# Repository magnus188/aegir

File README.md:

Ægir is a work-in-progress trimix gas analyzer for technical diving. It is not
qualified as a breathing-gas safety instrument; use it at your own risk.

Made in Norway 🇳🇴.

## The name

In Norse mythology, Ægir (/ˈæːɣir/) is the giant who rules the sea. He is
known for hosting the gods in his halls adorned with gold and, together with
Rán, is the father of nine daughters who personify the waves.

The runes ᛅᛁᚾ are a Viking Age-style representation of einn, Old Norse for
“one”, marking the first version of the project: Ægir 1.

## Features

- Oxygen (O₂) and helium (He) sensor inputs, plus CO monitoring
- 4.3-inch touch screen for gas analysis, calibration and settings
- Mix calculations, dive planning and analysis history
- Desktop simulator with demo readings

**[Try the interactive browser demo](https://magnus188.github.io/aegir/).**

## Device design

*CAD-based render of the current prototype.*

## Screenshots

These screens show the simulator with demo data.

| Main menu | Live analysis | Analysis details |
| :---: | :---: | :---: |
|  |  |  |

| History | Cylinders | Settings |
| :---: | :---: | :---: |
|  |  |  |

| Dive Planner | Device Settings |
| :---: | :---: |
|  |  |

| Simulated high CO alert | Safety Settings |
| :---: | :---: |
|  |  |

## Run it

For the desktop simulator, install a C++ compiler, CMake, `pkg-config` and SDL2,
then run from the repository root:

```sh
make sim-deps
make sim ZOOM=0.75
```

Run the host tests with `make test`.

To build and flash the firmware on the Guition JC4880P443C_I_W ESP32-P4 board,
install Python 3.13 and run:

```sh
make setup-idf
make devices
make board-info PORT=/dev/cu.usbserial-110
make push PORT=/dev/cu.usbserial-110
```

Replace the example `PORT` with the port reported by `make devices`. See the
[firmware guide](software/firmware/README.md) for other build options.

## Contributing and future ideas

Design reviews, measurements, documentation and software fixes are welcome.
Start with the [contribution guide](CONTRIBUTING.md) and
[open issues](https://github.com/magnus188/aegir/issues). The
[v2 investigation backlog](https://github.com/magnus188/aegir/milestone/1)
collects community suggestions without promising a release date.

Maintainers can use the [repository guide](.github/MAINTAINING.md). For
exploitable vulnerabilities, use the [private reporting route](SECURITY.md).

## Acknowledgements

A big thank you to [@tobiasruber](https://github.com/tobiasruber) for reviewing and
improving the PCB design. His help is a big reason this project is still alive
and moving forward.

## License

Software: [GPLv3](LICENSES/GPL-3.0-only.txt). PCB and CAD files:
[CERN-OHL-S-2.0](LICENSES/CERN-OHL-S-2.0.txt). The Ægir name and logo have a
separate [brand policy](logo/LICENSE.md). See the [license map](LICENSE.md)
for details and third-party files.

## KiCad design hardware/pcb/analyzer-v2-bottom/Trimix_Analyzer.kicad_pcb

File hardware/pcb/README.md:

# PCB designs

Open the active KiCad projects from their source folders:

| Board | Project | Purpose |
| --- | --- | --- |
| Main analyzer | [Trimix_Analyzer.kicad_pro](analyzer/Trimix_Analyzer.kicad_pro) | Current routed analyzer board, schematic sheets, and libraries |
| USB input | [Trimix_USB_Input.kicad_pro](usb-input/Trimix_USB_Input.kicad_pro) | Separate USB input daughterboard |

The [main-board manufacturing review](../system-review/electrical/main-final/README.md)
contains CAM files, assembly lists, stencil instructions, and a required
fill-and-cap hole map. **Prototype order remains on hold** pending the
[whole-system acceptance review](../system-review/README.md).

Project-created schematics, PCB layouts, libraries, and design exports are
licensed under [CERN-OHL-S-2.0](../../LICENSES/CERN-OHL-S-2.0.txt). The
[license map](../../LICENSE.md) lists exceptions for third-party reference
documents and models.

Earlier power-board and migration projects are available in Git history.
KiCad `.kicad_prl` files, locks, autosaves and backup folders are local editor
state and are ignored by Git.

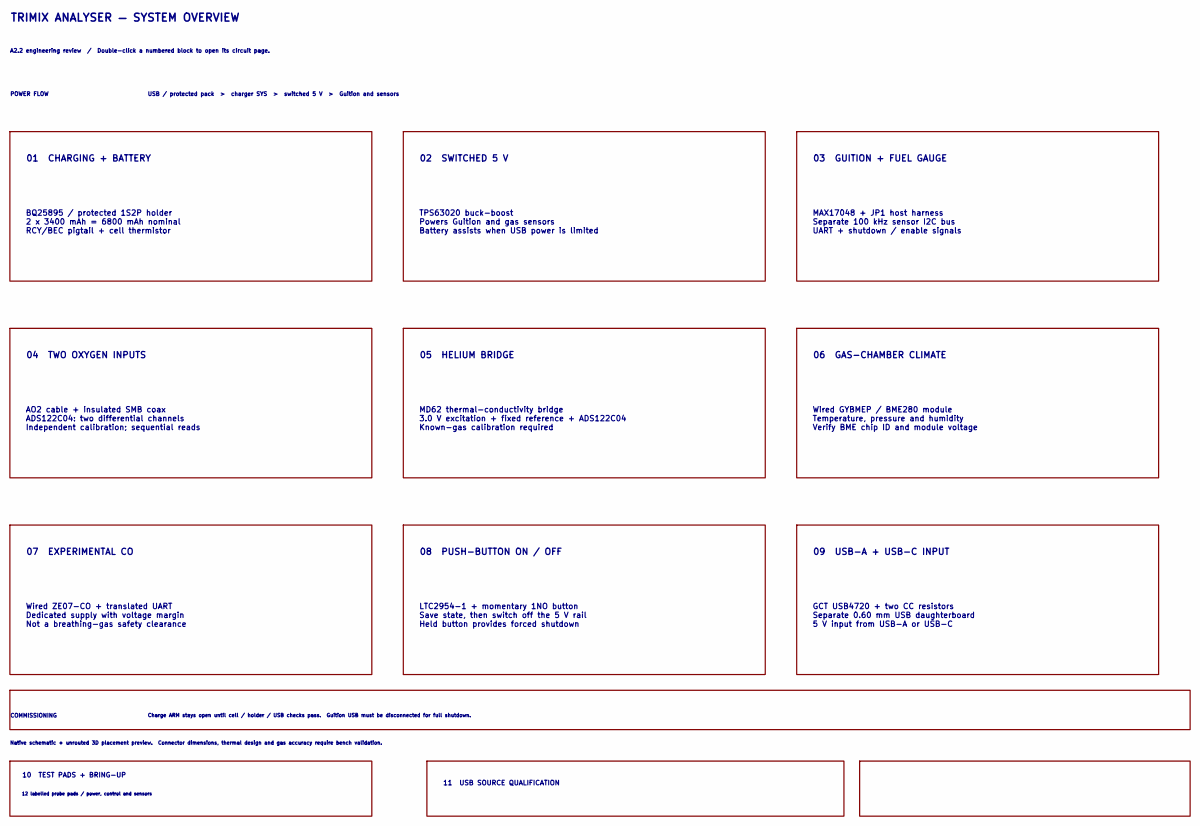
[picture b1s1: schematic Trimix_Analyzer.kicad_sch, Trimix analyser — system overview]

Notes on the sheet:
AO2 cable + insulated SMB coax ADS122C04: two differential channels Independent calibration; sequential reads
Charge ARM stays open until cell / holder / USB checks pass. Guition USB must be disconnected for full shutdown.
12 labelled probe pads / power, control and sensors
BQ25895 / protected 1S2P holder 2 x 3400 mAh = 6800 mAh nominal RCY/BEC pigtail + cell thermistor
TPS63020 buck-boost Powers Guition and gas sensors Battery assists when USB power is limited
MAX17048 + JP1 host harness Separate 100 kHz sensor I2C bus UART + shutdown / enable signals
GCT USB4720 + two CC resistors Separate 0.60 mm USB daughterboard 5 V input from USB-A or USB-C
05 HELIUM BRIDGE
COMMISSIONING
Wired ZE07-CO + translated UART Dedicated supply with voltage margin Not a breathing-gas safety clearance
Wired GYBMEP / BME280 module Temperature, pressure and humidity Verify BME chip ID and module voltage
LTC2954-1 + momentary 1NO button Save state, then switch off the 5 V rail Held button provides forced shutdown
02 SWITCHED 5 V
Native schematic + unrouted 3D placement preview. Connector dimensions, thermal design and gas accuracy require bench validation.
07 EXPERIMENTAL CO
06 GAS-CHAMBER CLIMATE
01 CHARGING + BATTERY
08 PUSH-BUTTON ON / OFF
MD62 thermal-conductivity bridge 3.0 V excitation + fixed reference + ADS122C04 Known-gas calibration required
POWER FLOW
09 USB-A + USB-C INPUT
TRIMIX ANALYSER — SYSTEM OVERVIEW
04 TWO OXYGEN INPUTS
11 USB SOURCE QUALIFICATION
03 GUITION + FUEL GAUGE
A2.2 engineering review / Double-click a numbered block to open its circuit page.
USB / protected pack > charger SYS > switched 5 V > Guition and sensors
10 TEST PADS + BRING-UP

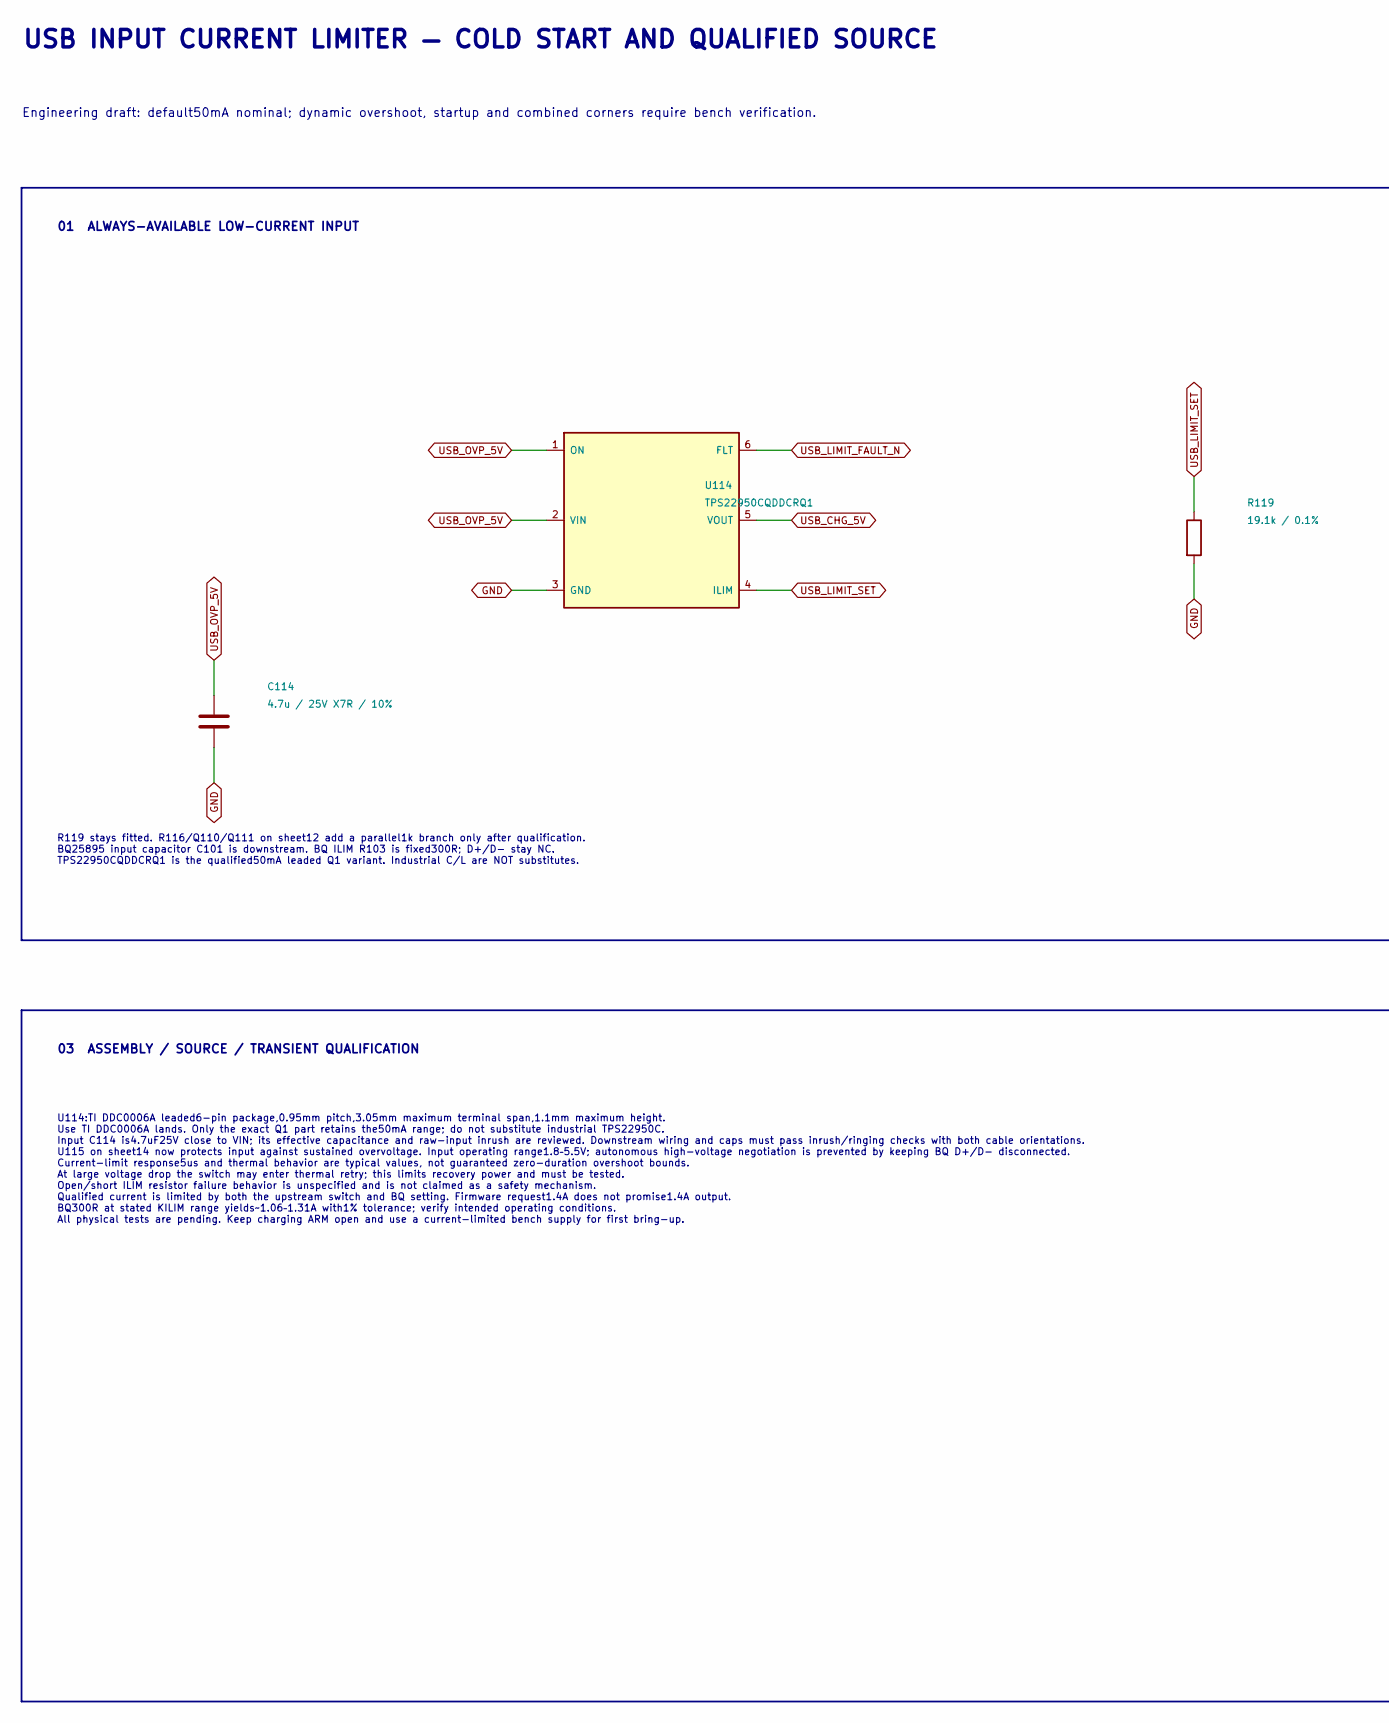
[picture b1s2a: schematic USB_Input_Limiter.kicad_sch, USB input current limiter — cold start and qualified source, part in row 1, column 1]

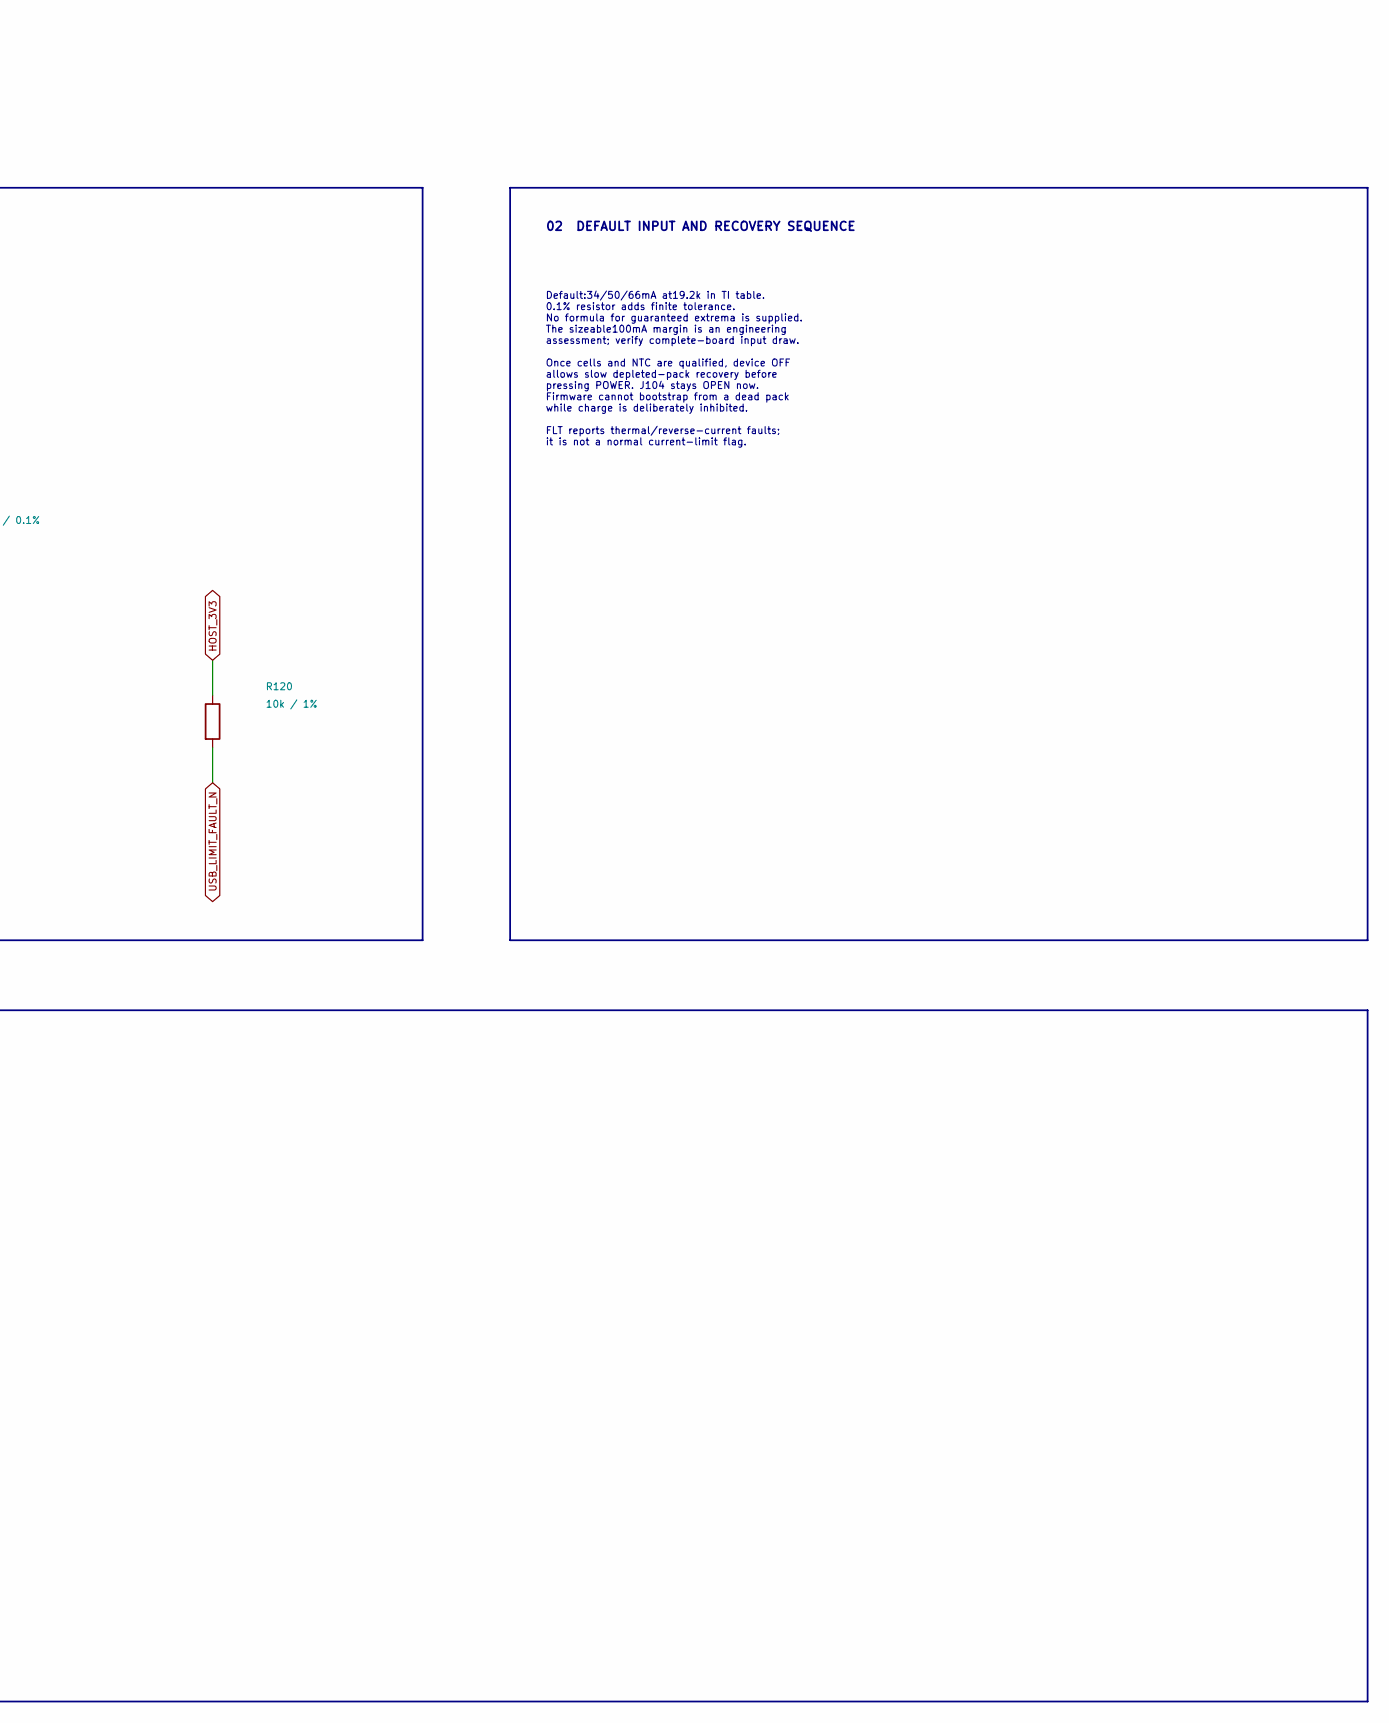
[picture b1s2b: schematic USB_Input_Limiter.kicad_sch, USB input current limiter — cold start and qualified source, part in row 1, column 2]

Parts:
C114: 4.7u / 25V X7R / 10%; C_1206_3216Metric; MPN C3216X7R1E475K160AC
R119: 19.1k / 0.1%; R_0402_1005Metric; Voltage_rating_note Continuous voltage also limited by dera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; MPN RT0402BRD0719K1L
R120: 10k / 1%; R_0603_1608Metric; MPN RC0603FR-0710KL
U114: TPS22950CQDDCRQ1; TI_DDC0006A; MPN TPS22950CQDDCRQ1

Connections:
GND: C114.2, R119.2, U114.3 (GND); also elsewhere on the board
HOST_3V3: R120.1; also elsewhere on the board
USB_CHG_5V: U114.5 (VOUT); also elsewhere on the board
USB_LIMIT_FAULT_N: R120.2, U114.6 (FLT)
USB_LIMIT_SET: R119.1, U114.4 (ILIM); also elsewhere on the board
USB_OVP_5V: C114.1, U114.1 (ON), U114.2 (VIN); also elsewhere on the board

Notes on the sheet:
02 DEFAULT INPUT AND RECOVERY SEQUENCE
USB INPUT CURRENT LIMITER — COLD START AND QUALIFIED SOURCE
03 ASSEMBLY / SOURCE / TRANSIENT QUALIFICATION
Engineering draft: default50mA nominal; dynamic overshoot, startup and combined corners require bench verification.
U114:TI DDC0006A leaded6-pin package,0.95mm pitch,3.05mm maximum terminal span,1.1mm maximum height. Use TI DDC0006A lands. Only the exact Q1 part retains the50mA range; do not substitute industrial TPS22950C. Input C114 is4.7uF25V close to VIN; its effective capacitance and raw-input inrush are re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
Default:34/50/66mA at19.2k in TI table. 0.1% resistor adds finite tolerance. No formula for guaranteed extrema is supplied. The sizeable100mA margin is an engineering assessment; verify complete-board input draw. Once cells and NTC are qualified, device OFF allows slow depleted-pack recovery before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
01 ALWAYS-AVAILABLE LOW-CURRENT INPUT
R119 stays fitted. R116/Q110/Q111 on sheet12 add a parallel1k branch only after qualification. BQ25895 input capacitor C101 is downstream. BQ ILIM R103 is fixed300R; D+/D- stay NC. TPS22950CQDDCRQ1 is the qualified50mA leaded Q1 variant. Industrial C/L are NOT substitutes.

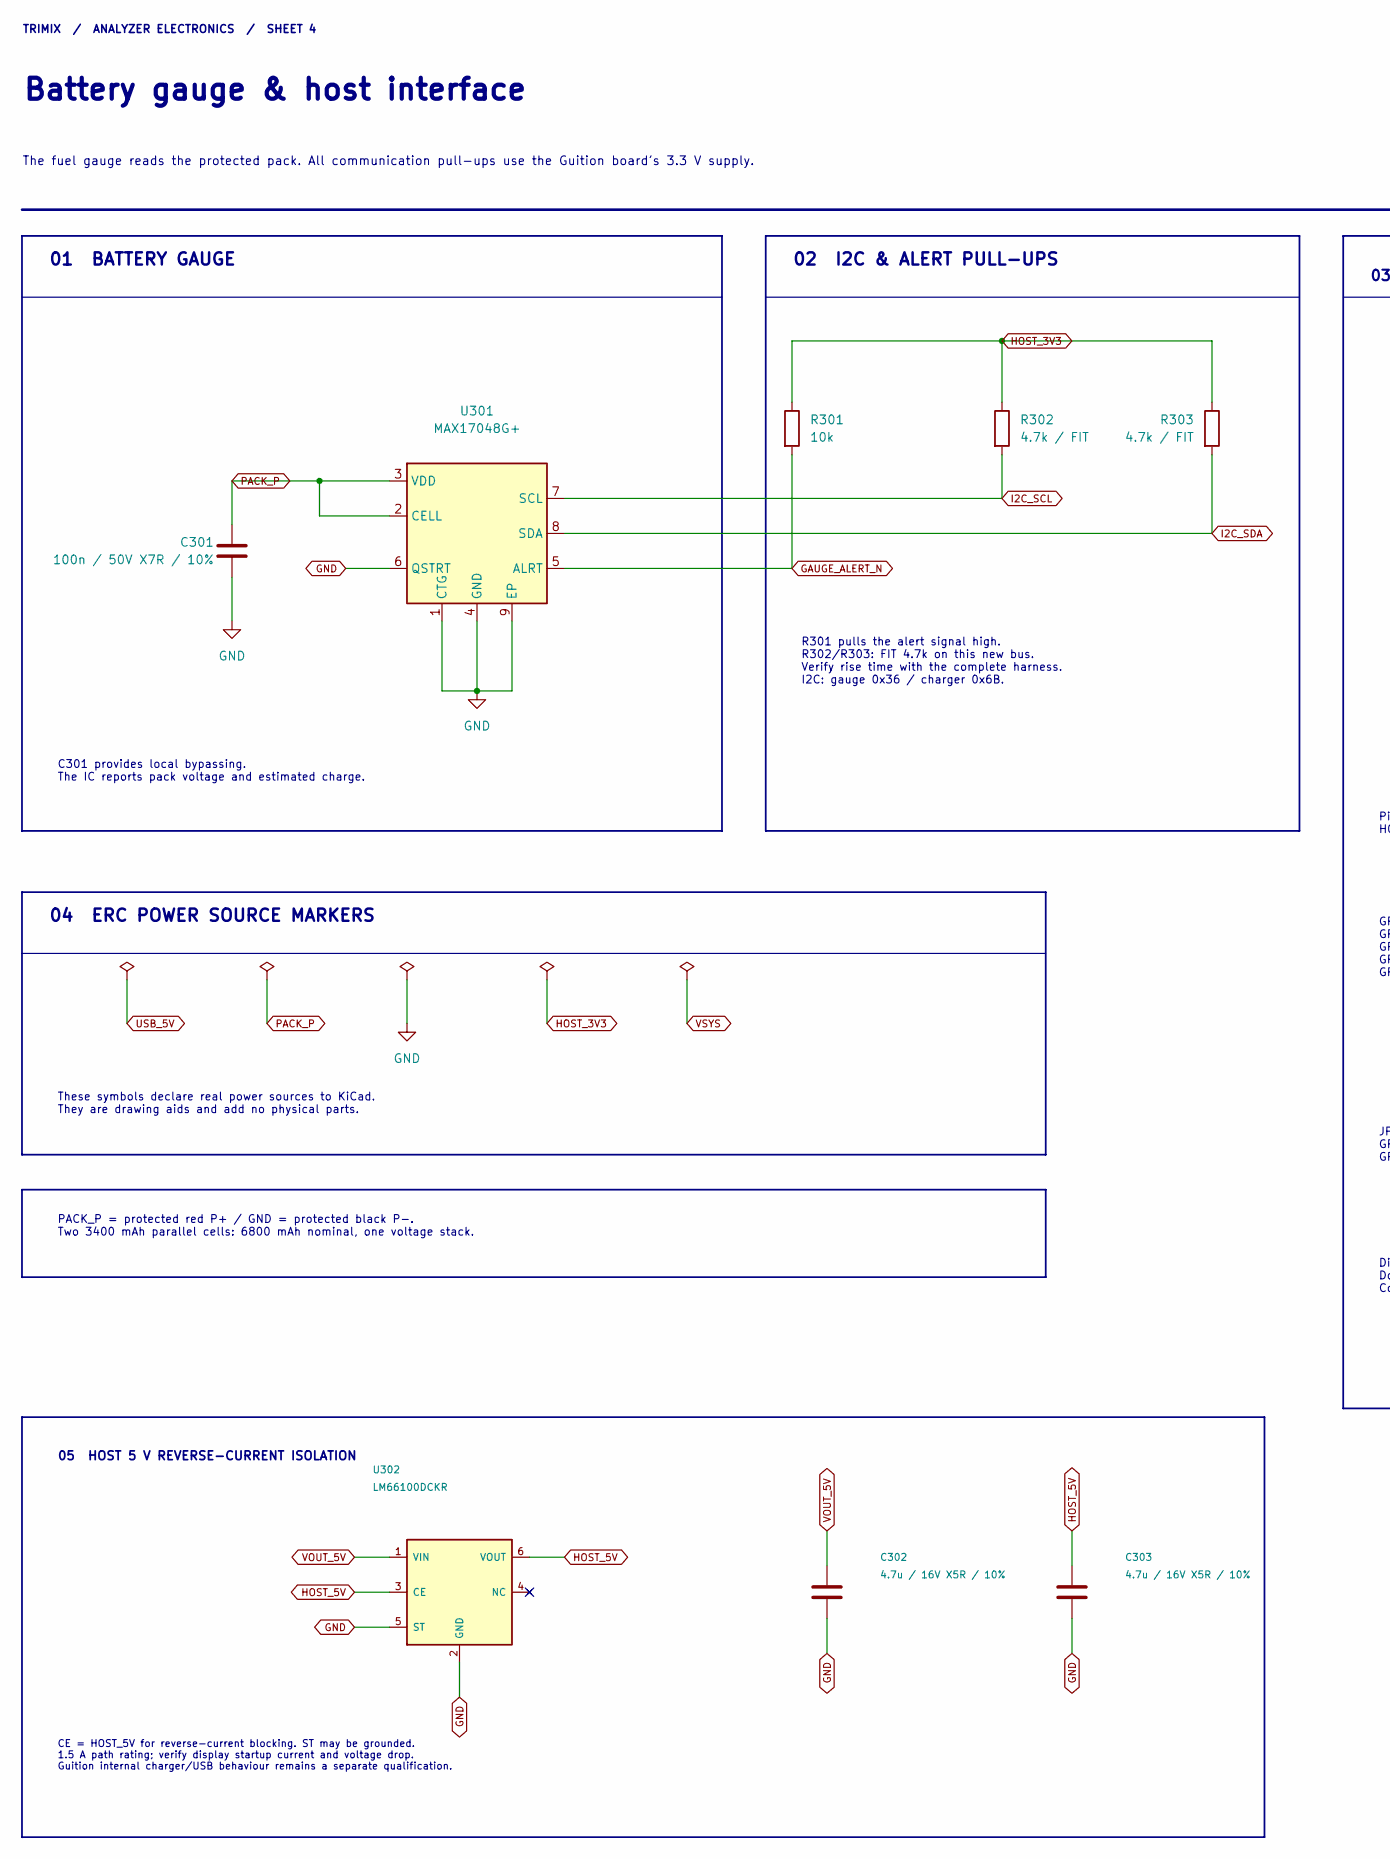
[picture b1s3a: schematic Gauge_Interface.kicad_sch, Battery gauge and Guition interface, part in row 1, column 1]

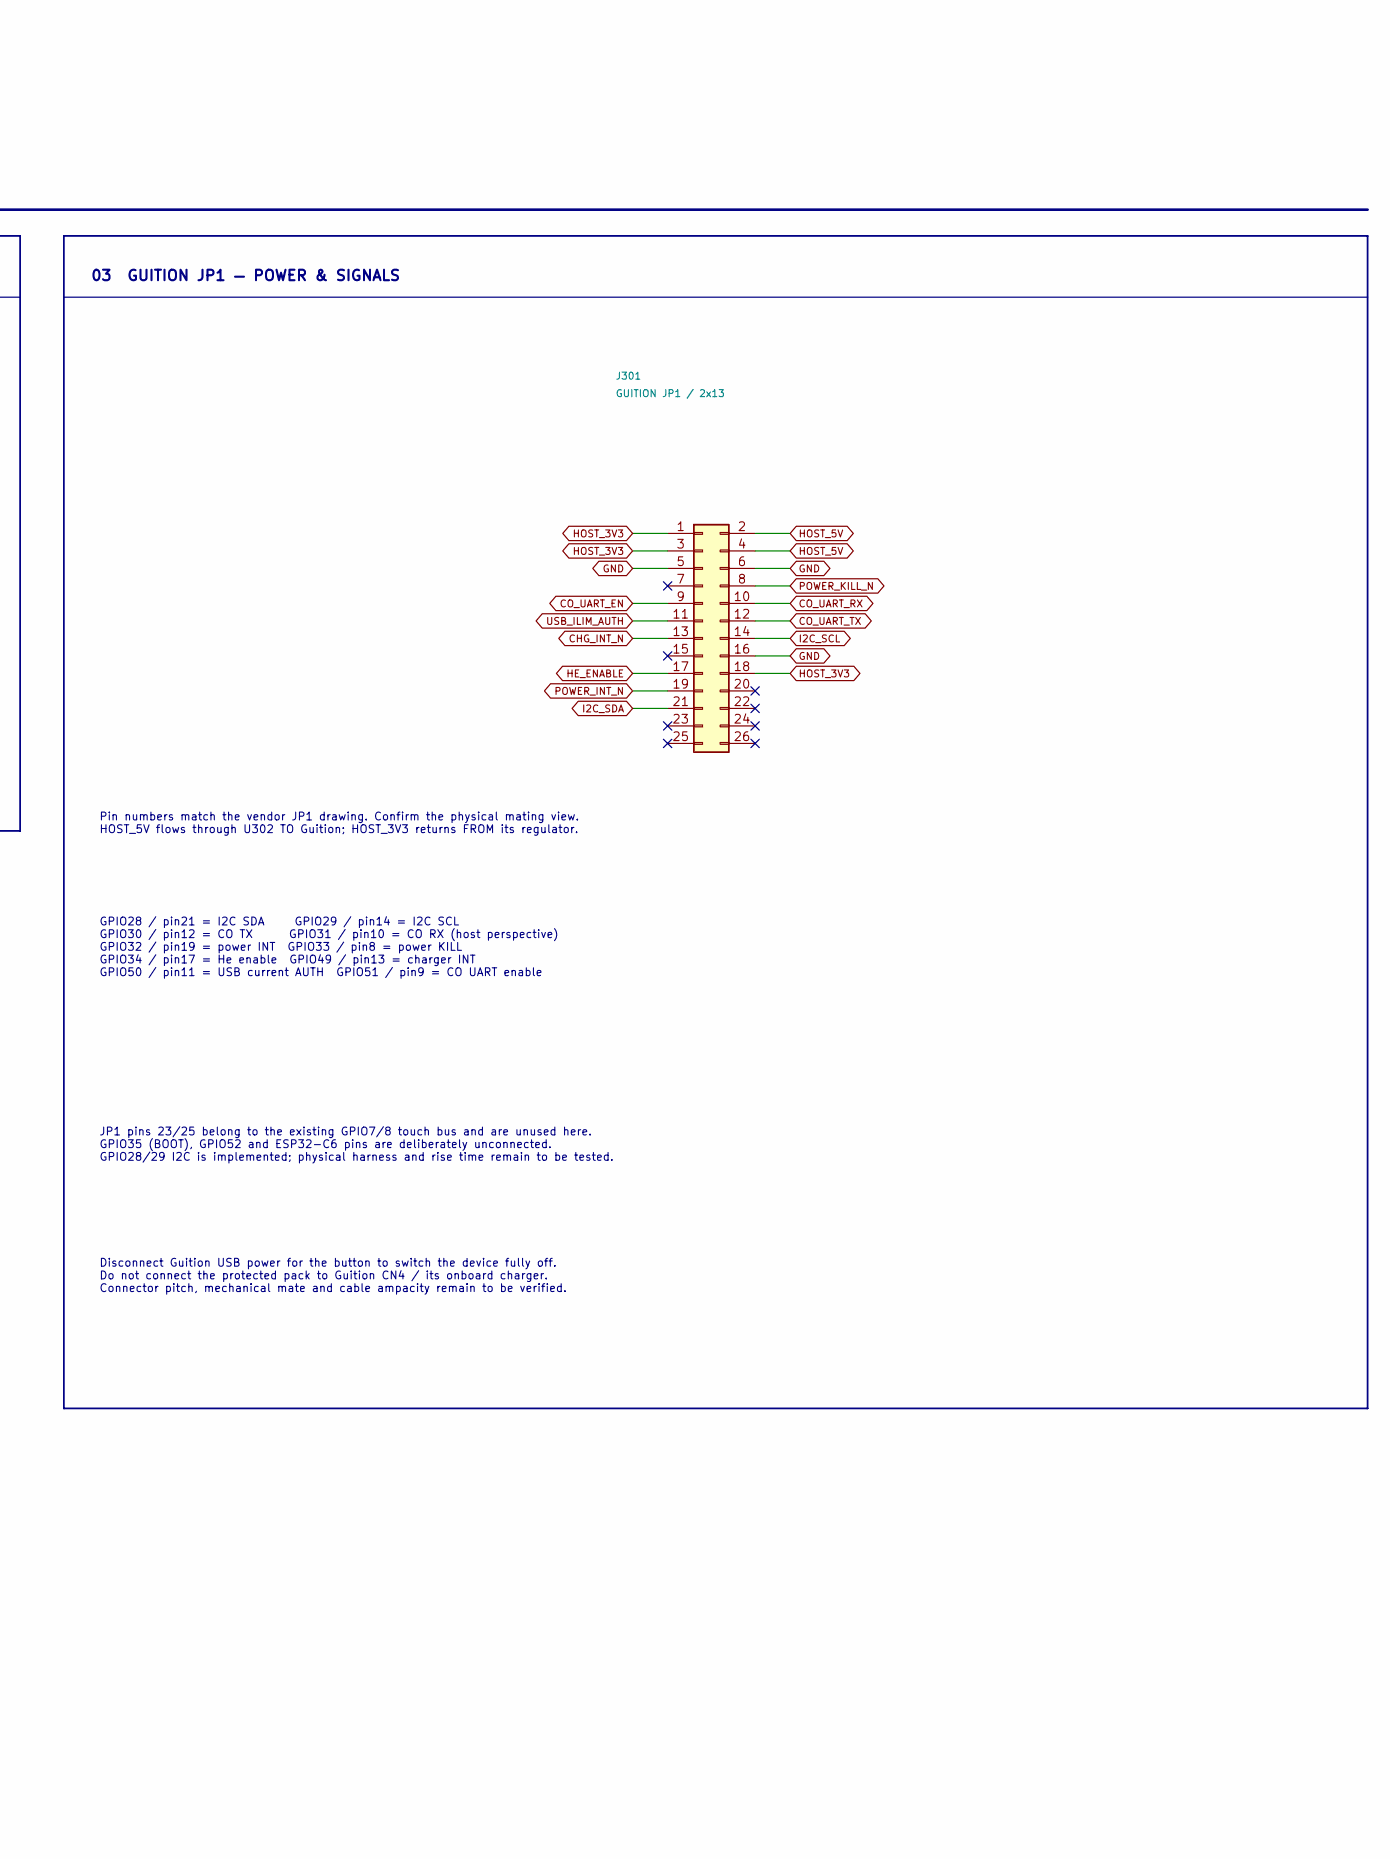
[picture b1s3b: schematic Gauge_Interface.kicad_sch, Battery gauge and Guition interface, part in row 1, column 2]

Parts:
C301: 100n / 50V X7R / 10%; C_0805_2012Metric; MPN C0805C104K5RACTU
C302, C303: 4.7u / 16V X5R / 10%; C_0603_1608Metric; MPN C1608X5R1C475K080AC
J301: GUITION JP1 / 2x13; Samtec_HTSW-113-07-L-D-007_P2.54mm_Key7; MPN HTSW-113-07-L-D-007
R301: 10k; R_0603_1608Metric; MPN RC0603FR-0710KL
R302, R303: 4.7k / FIT; R_0603_1608Metric; MPN RC0603FR-074K7L
U301: MAX17048G+; TDFN-8-1EP_2x2mm_P0.5mm_EP0.8x1.2mm; MPN MAX17048G+T10
U302: LM66100DCKR; SOT-363_SC-70-6; MPN LM66100DCKR

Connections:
CHG_INT_N: J301.13; also elsewhere on the board
CO_UART_EN: J301.9; also elsewhere on the board
CO_UART_RX: J301.10; also elsewhere on the board
CO_UART_TX: J301.12; also elsewhere on the board
GAUGE_ALERT_N: R301.2, U301.5 (ALRT)
GND: C301.2, C302.2, C303.2, J301.5, J301.6, J301.16, U301.1 (CTG), U301.4 (GND), U301.6 (QSTRT), U301.9 (EP), U302.2 (GND), U302.5 (ST); also elsewhere on the board
HE_ENABLE: J301.17; also elsewhere on the board
HOST_3V3: J301.1, J301.3, J301.18, R301.1, R302.1, R303.1; also elsewhere on the board
HOST_5V: C303.1, J301.2, J301.4, U302.3 (CE), U302.6 (VOUT)
I2C_SCL: J301.14, R302.2, U301.7 (SCL); also elsewhere on the board
I2C_SDA: J301.21, R303.2, U301.8 (SDA); also elsewhere on the board
PACK_P: C301.1, U301.2 (CELL), U301.3 (VDD); also elsewhere on the board
POWER_INT_N: J301.19; also elsewhere on the board
POWER_KILL_N: J301.8; also elsewhere on the board
USB_ILIM_AUTH: J301.11; also elsewhere on the board
VOUT_5V: C302.1, U302.1 (VIN); also elsewhere on the board

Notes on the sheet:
Pin numbers match the vendor JP1 drawing. Confirm the physical mating view. HOST_5V flows through U302 TO Guition; HOST_3V3 returns FROM its regulator.
C301 provides local bypassing. The IC reports pack voltage and estimated charge.
CE = HOST_5V for reverse-current blocking. ST may be grounded. 1.5 A path rating; verify display startup current and voltage drop. Guition internal charger/USB behaviour remains a separate qualification.
TRIMIX / ANALYZER ELECTRONICS / SHEET 4
The fuel gauge reads the protected pack. All communication pull-ups use the Guition board's 3.3 V supply.
04 ERC POWER SOURCE MARKERS
03 GUITION JP1 — POWER & SIGNALS
Battery gauge & host interface
These symbols declare real power sources to KiCad. They are drawing aids and add no physical parts.
GPIO28 / pin21 = I2C SDA GPIO29 / pin14 = I2C SCL GPIO30 / pin12 = CO TX GPIO31 / pin10 = CO RX (host perspective) GPIO32 / pin19 = power INT GPIO33 / pin8 = power KILL GPIO34 / pin17 = He enable GPIO49 / pin13 = charger INT GPIO50 / pin11 = USB current AUTH GPIO51 / pin9 = CO UART enable
01 BATTERY GAUGE
R301 pulls the alert signal high. R302/R303: FIT 4.7k on this new bus. Verify rise time with the complete harness. I2C: gauge 0x36 / charger 0x6B.
02 I2C & ALERT PULL-UPS
JP1 pins 23/25 belong to the existing GPIO7/8 touch bus and are unused here. GPIO35 (BOOT), GPIO52 and ESP32-C6 pins are deliberately unconnected. GPIO28/29 I2C is implemented; physical harness and rise time remain to be tested.
05 HOST 5 V REVERSE-CURRENT ISOLATION
PACK_P = protected red P+ / GND = protected black P-. Two 3400 mAh parallel cells: 6800 mAh nominal, one voltage stack.
Disconnect Guition USB power for the button to switch the device fully off. Do not connect the protected pack to Guition CN4 / its onboard charger. Connector pitch, mechanical mate and cable ampacity remain to be verified.

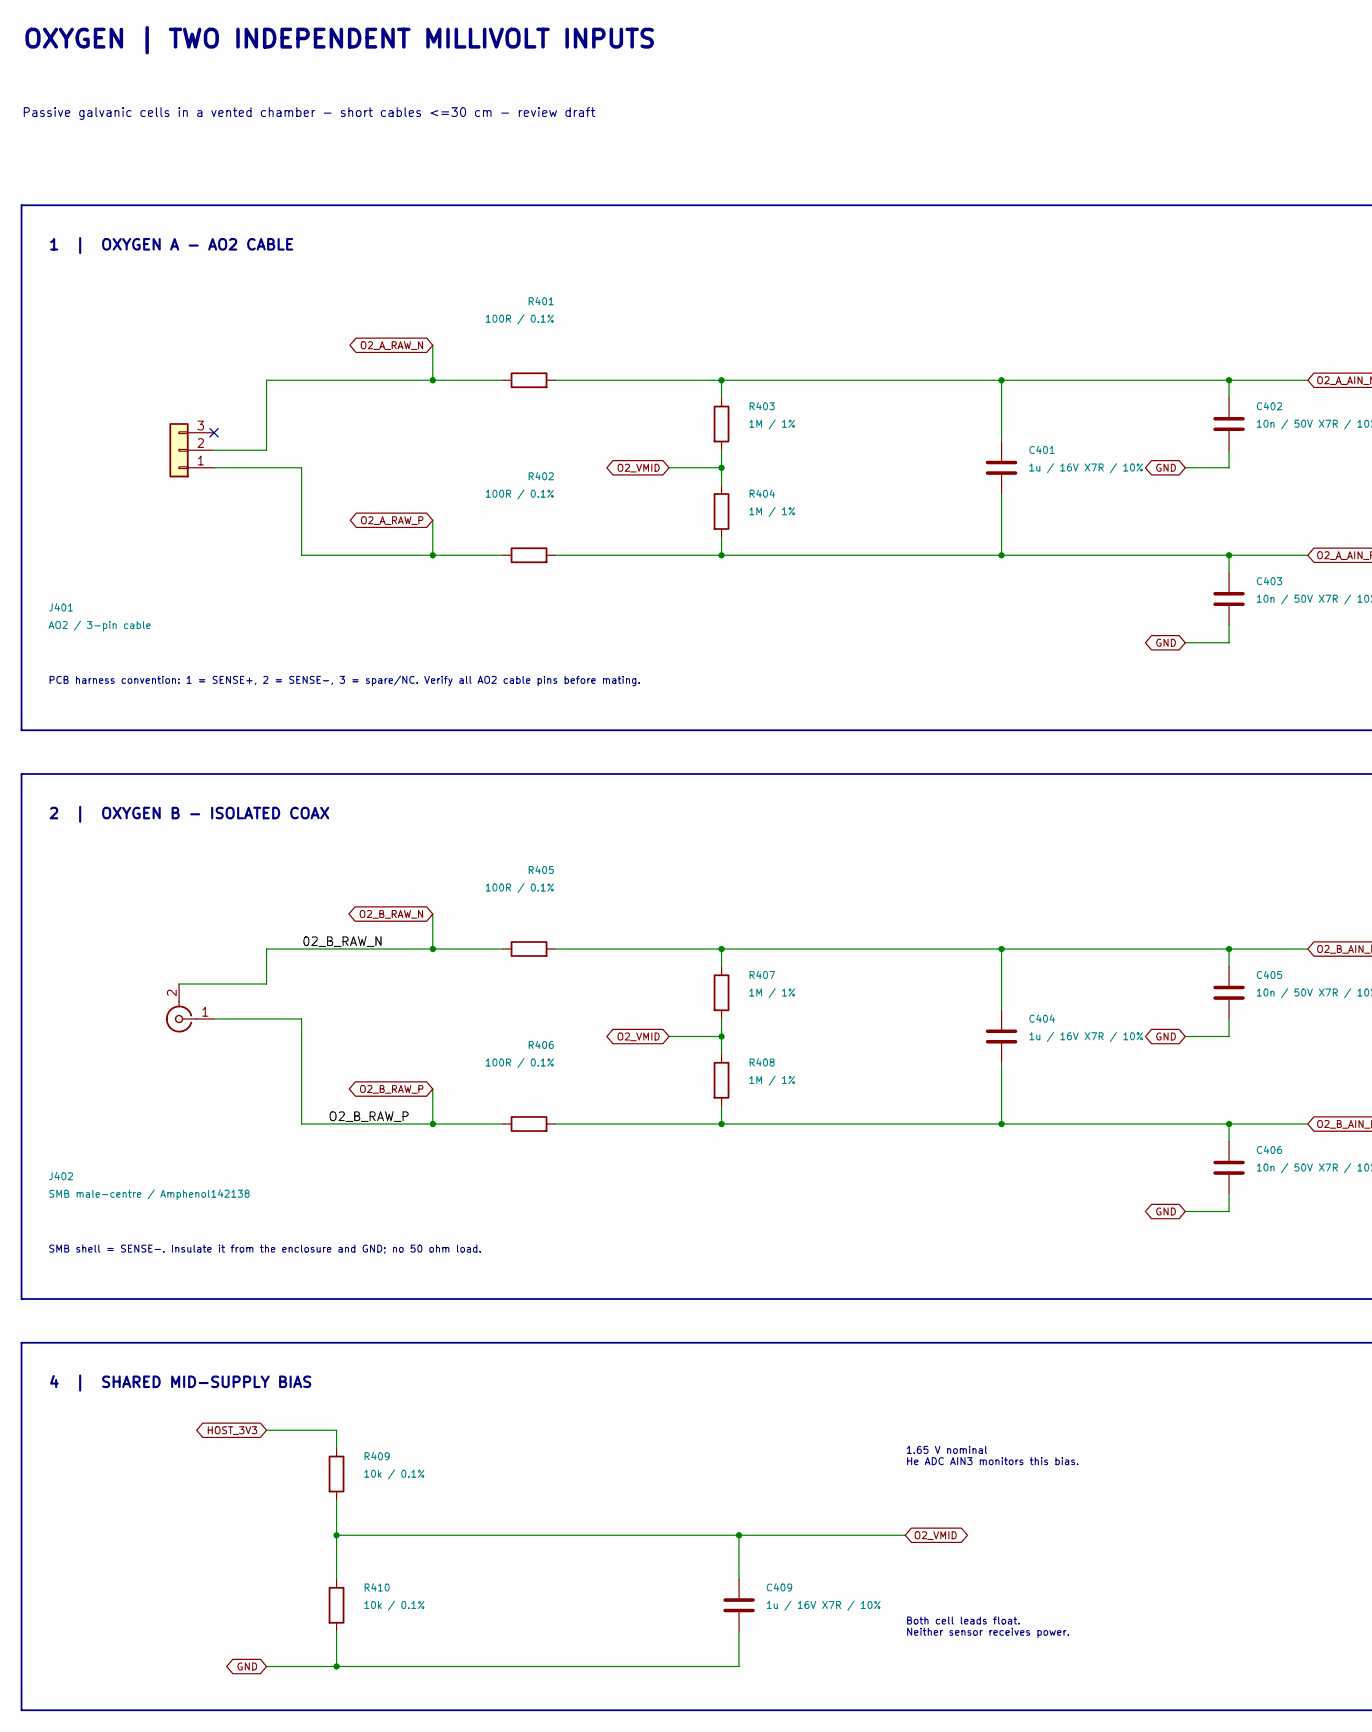
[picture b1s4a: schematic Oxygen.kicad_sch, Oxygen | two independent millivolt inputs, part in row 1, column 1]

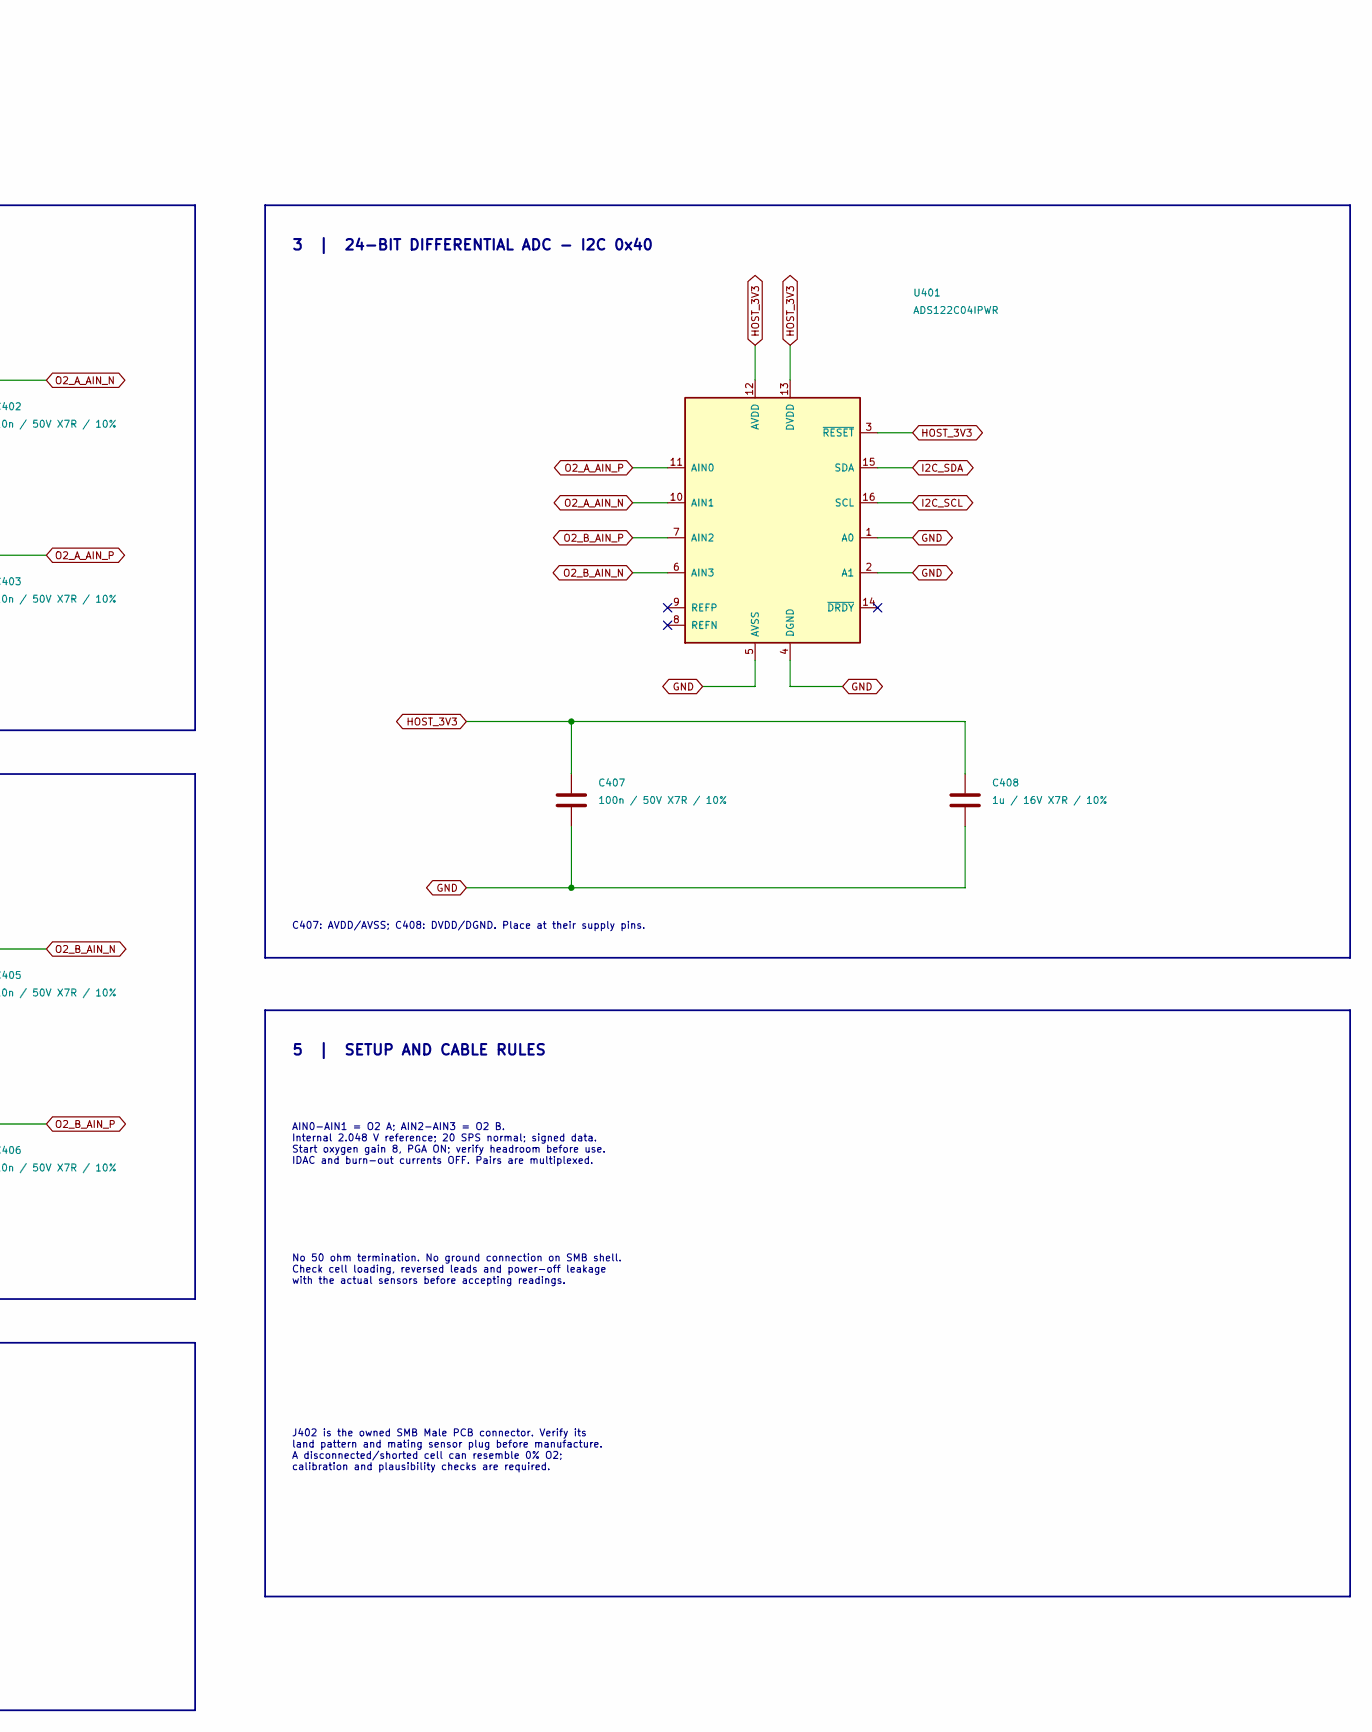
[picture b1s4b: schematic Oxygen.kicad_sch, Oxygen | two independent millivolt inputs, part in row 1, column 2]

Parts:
C401, C404, C408, C409: 1u / 16V X7R / 10%; C_0603_1608Metric; MPN C0603C105K4RACTU
C402, C403, C405, C406: 10n / 50V X7R / 10%; C_0603_1608Metric; MPN C1608X7R1H103K080AA
C407: 100n / 50V X7R / 10%; C_0603_1608Metric; MPN C1608X7R1H104K080AA
J401: AO2 / 3-pin cable; PinHeader_1x03_P2.54mm_Vertical; MPN M20-9990346
J402: SMB male-centre / Amphenol142138; SMB_Amphenol_142138; MPN 142138
R401, R402, R405, R406: 100R / 0.1%; R_0603_1608Metric; MPN RT0603BRD07100RL
R403, R404, R407, R408: 1M / 1%; R_0603_1608Metric; MPN RC0603FR-071ML
R409, R410: 10k / 0.1%; R_0603_1608Metric; MPN RT0603BRD0710KL
U401: ADS122C04IPWR; TSSOP-16_4.4x5mm_P0.65mm; MPN ADS122C04IPWR

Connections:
GND: C402.2, C403.2, C405.2, C406.2, C407.2, C408.2, C409.2, R410.2, U401.1 (A0), U401.2 (A1), U401.4 (DGND), U401.5 (AVSS); also elsewhere on the board
HOST_3V3: C407.1, C408.1, R409.1, U401.3 (~RESET), U401.12 (AVDD), U401.13 (DVDD); also elsewhere on the board
I2C_SCL: U401.16 (SCL); also elsewhere on the board
I2C_SDA: U401.15 (SDA); also elsewhere on the board
O2_A_AIN_N: C401.1, C402.1, R401.2, R403.1, U401.10 (AIN1)
O2_A_AIN_P: C401.2, C403.1, R402.2, R404.2, U401.11 (AIN0)
O2_A_RAW_N: J401.2, R401.1
O2_A_RAW_P: J401.1, R402.1
O2_B_AIN_N: C404.1, C405.1, R405.2, R407.1, U401.6 (AIN3)
O2_B_AIN_P: C404.2, C406.1, R406.2, R408.2, U401.7 (AIN2)
O2_B_RAW_N: J402.2 (Ext), R405.1
O2_B_RAW_P: J402.1 (In), R406.1
O2_VMID: C409.1, R403.2, R404.1, R407.2, R408.1, R409.2, R410.1; also elsewhere on the board

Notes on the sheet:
PCB harness convention: 1 = SENSE+, 2 = SENSE-, 3 = spare/NC. Verify all AO2 cable pins before mating.
SMB shell = SENSE-. Insulate it from the enclosure and GND; no 50 ohm load.
2 | OXYGEN B - ISOLATED COAX
No 50 ohm termination. No ground connection on SMB shell. Check cell loading, reversed leads and power-off leakage with the actual sensors before accepting readings.
4 | SHARED MID-SUPPLY BIAS
Both cell leads float. Neither sensor receives power.
1 | OXYGEN A - AO2 CABLE
AIN0-AIN1 = O2 A; AIN2-AIN3 = O2 B. Internal 2.048 V reference; 20 SPS normal; signed data. Start oxygen gain 8, PGA ON; verify headroom before use. IDAC and burn-out currents OFF. Pairs are multiplexed.
3 | 24-BIT DIFFERENTIAL ADC - I2C 0x40
5 | SETUP AND CABLE RULES
Passive galvanic cells in a vented chamber - short cables <=30 cm - review draft
C407: AVDD/AVSS; C408: DVDD/DGND. Place at their supply pins.
J402 is the owned SMB Male PCB connector. Verify its land pattern and mating sensor plug before manufacture. A disconnected/shorted cell can resemble 0% O2; calibration and plausibility checks are required.
OXYGEN | TWO INDEPENDENT MILLIVOLT INPUTS
1.65 V nominal He ADC AIN3 monitors this bias.
